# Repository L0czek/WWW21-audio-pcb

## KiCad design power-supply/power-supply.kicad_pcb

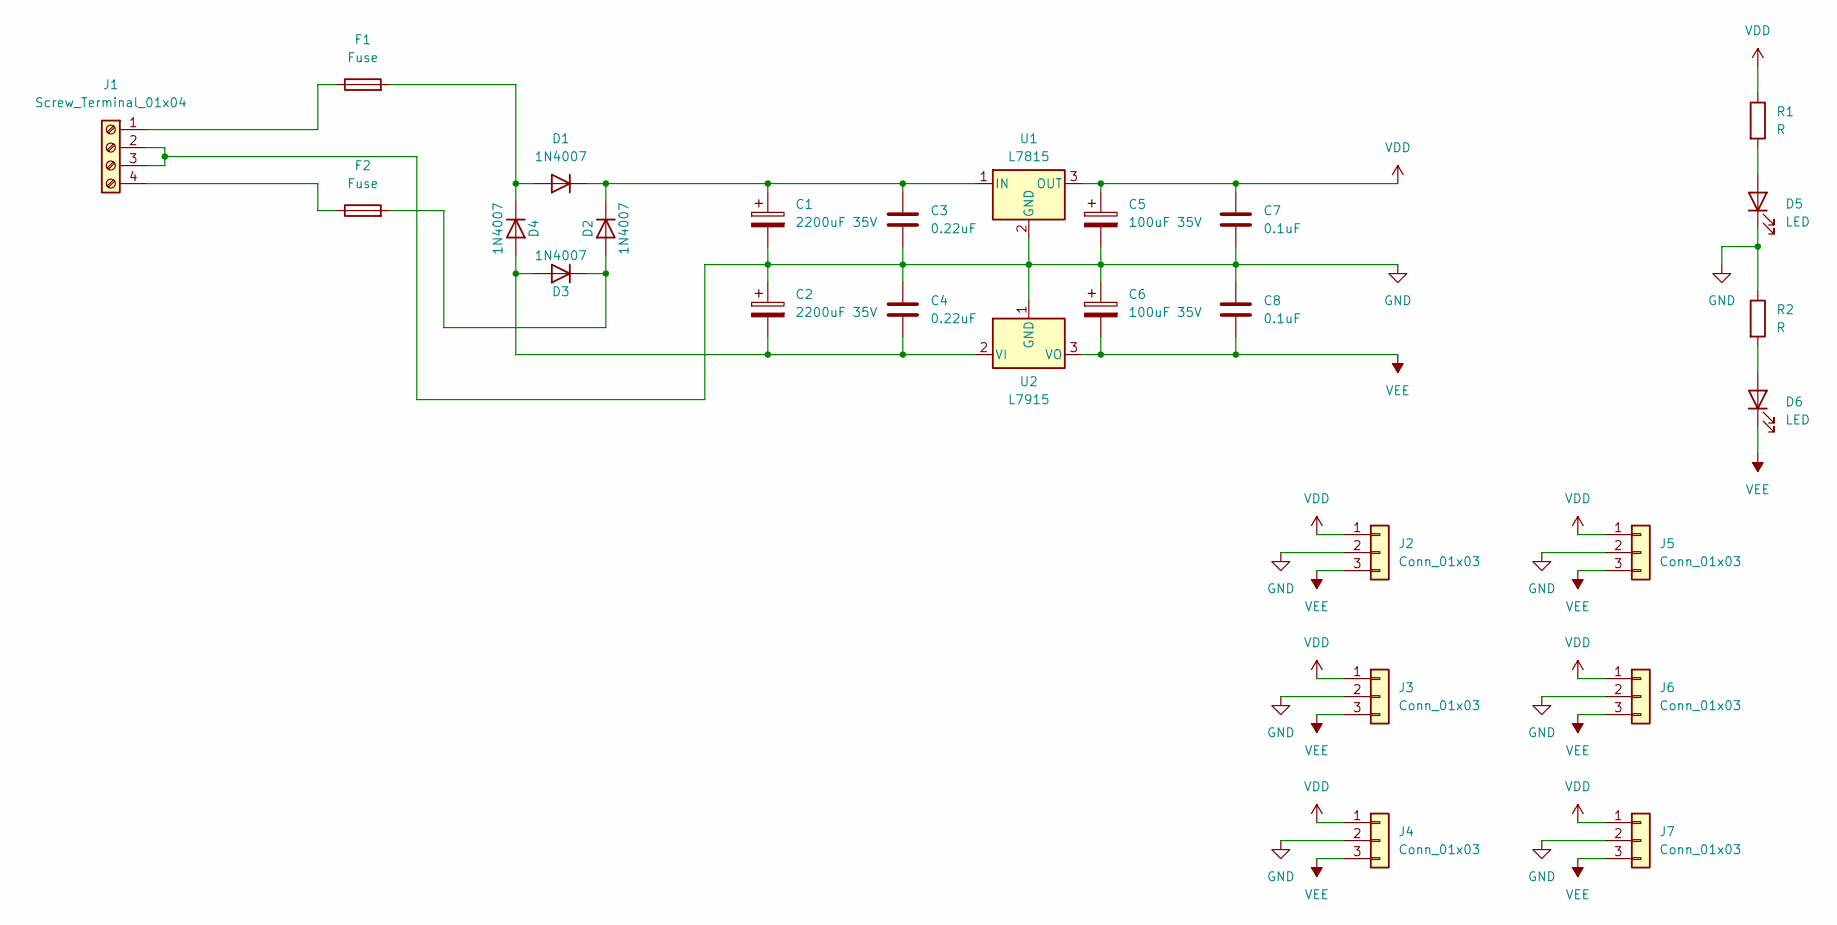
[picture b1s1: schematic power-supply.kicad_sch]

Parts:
C1, C2: 2200uF 35V; CP_Radial_D18.0mm_P7.50mm
C3, C4: 0.22uF; C_Disc_D5.0mm_W2.5mm_P5.00mm
C5, C6: 100uF 35V; CP_Radial_D10.0mm_P5.00mm
C7, C8: 0.1uF; C_Disc_D5.0mm_W2.5mm_P5.00mm
D1, D2, D3, D4: 1N4007; D_DO-41_SOD81_P10.16mm_Horizontal
D5, D6: LED; LED_D5.0mm
F1, F2: Fuse; R_Axial_DIN0207_L6.3mm_D2.5mm_P10.16mm_Horizontal
J1: Screw_Terminal_01x04; TerminalBlock_MaiXu_MX126-5.0-04P_1x04_P5.00mm
J2, J3, J4, J5, J6, J7: Conn_01x03; JST_PH_B3B-PH-K_1x03_P2.00mm_Vertical
R1, R2: R; R_Axial_DIN0207_L6.3mm_D2.5mm_P10.16mm_Horizontal
U1: L7815; TO-220-3_Vertical
U2: L7915; TO-220-3_Vertical

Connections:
GND: C1.2, C2.1, C3.2, C4.1, C5.2, C6.1, C7.2, C8.1, D5.1 (K), J1.2, J1.3, J2.2, J3.2, J4.2, J5.2, J6.2, J7.2, R2.1, U1.2 (GND), U2.1 (GND)
unnamed: D1.2 (A), D4.1 (K), F1.2
unnamed: C1.1, C3.1, D1.1 (K), D2.1 (K), U1.1 (IN)
unnamed: D2.2 (A), D3.1 (K), F2.2
unnamed: C2.2, C4.2, D3.2 (A), D4.2 (A), U2.2 (VI)
unnamed: D5.2 (A), R1.2
unnamed: D6.2 (A), R2.2
unnamed: F1.1, J1.1
unnamed: F2.1, J1.4
VDD: C5.1, C7.1, J2.1, J3.1, J4.1, J5.1, J6.1, J7.1, R1.1, U1.3 (OUT)
VEE: C6.2, C8.2, D6.1 (K), J2.3, J3.3, J4.3, J5.3, J6.3, J7.3, U2.3 (VO)

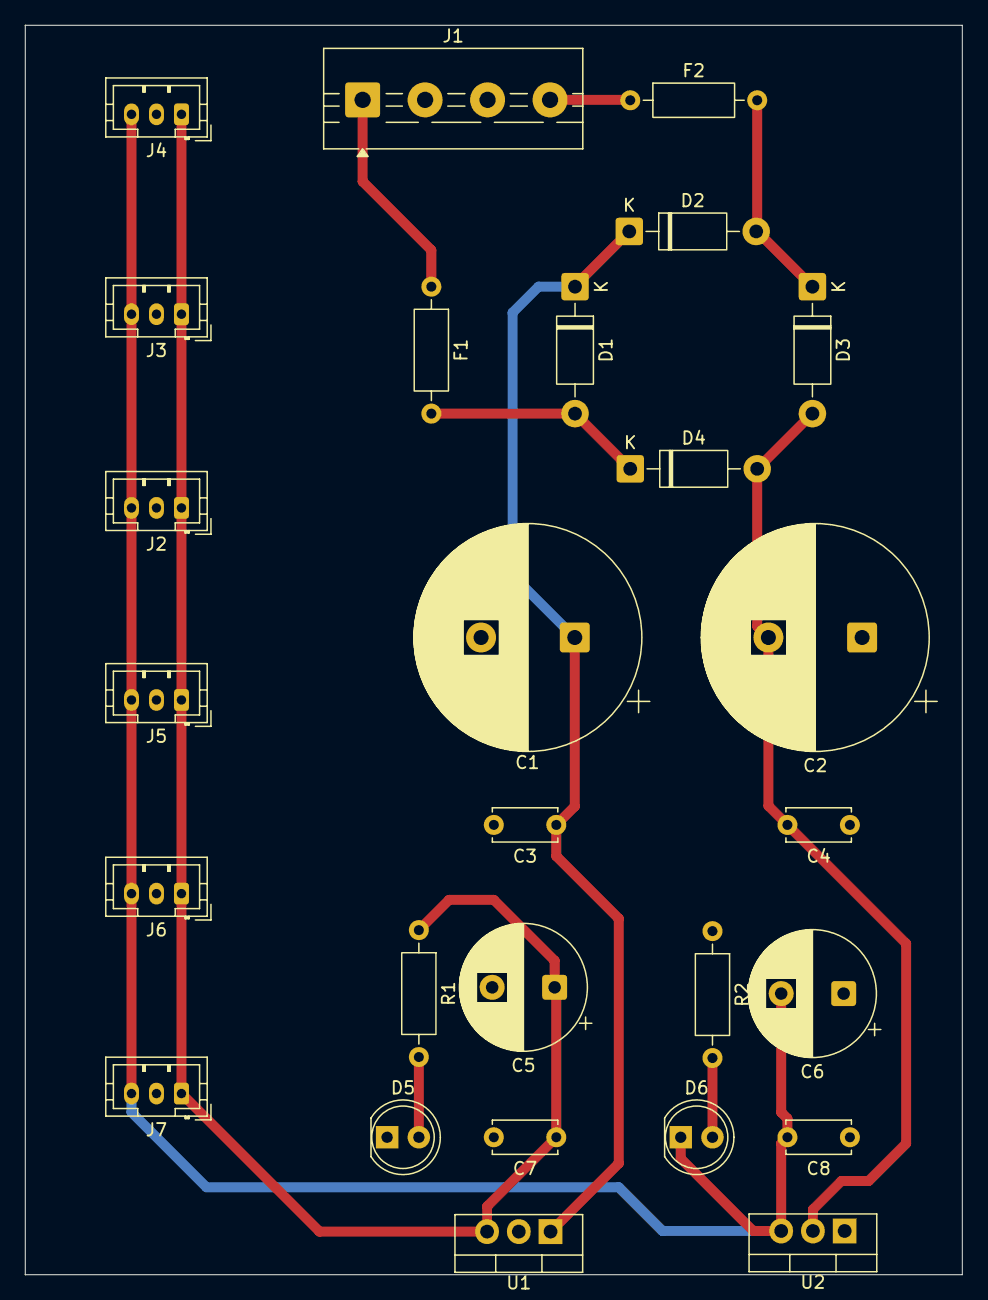
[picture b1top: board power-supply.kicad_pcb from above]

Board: 2 copper layers, 75.0 x 100.0 mm, 27 parts (0 on the bottom side), 11 nets.

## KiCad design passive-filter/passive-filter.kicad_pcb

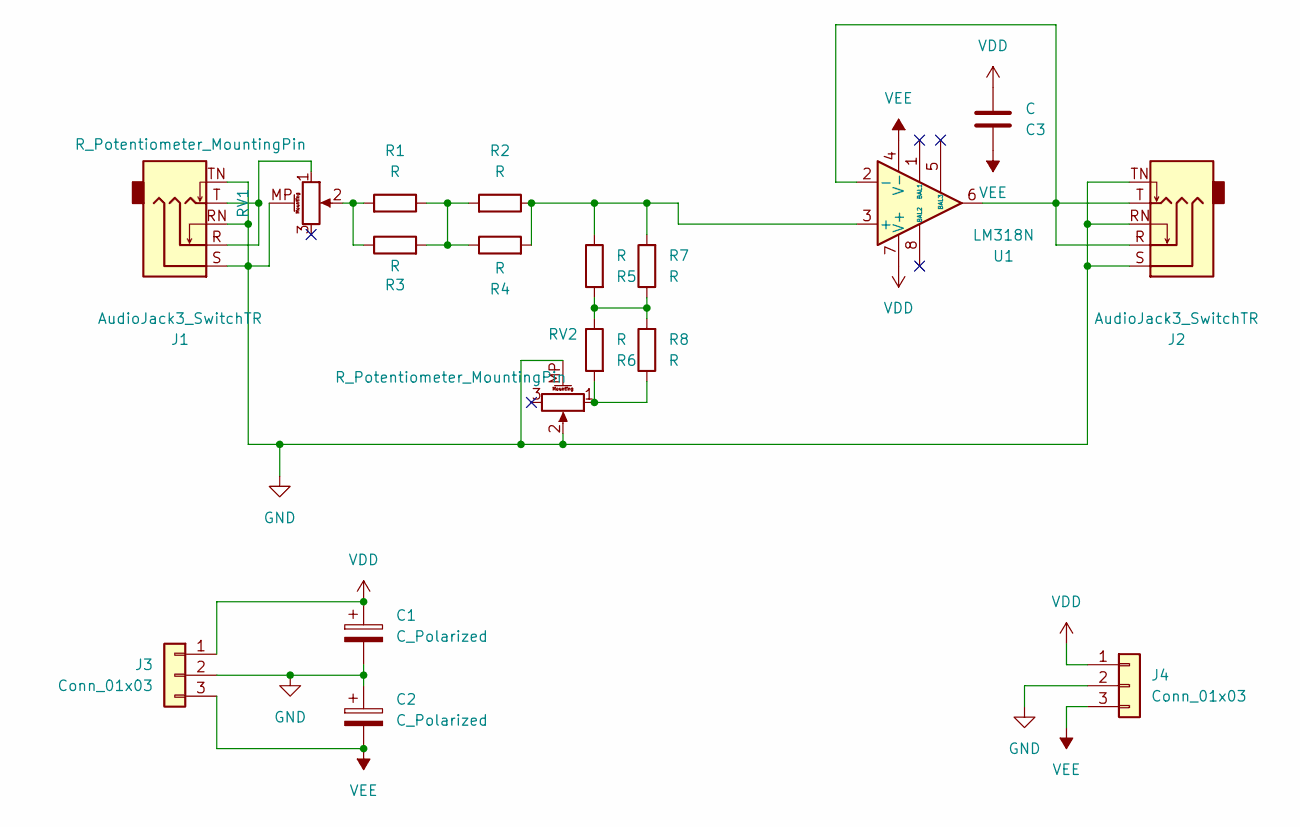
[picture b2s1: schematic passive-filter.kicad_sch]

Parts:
C1, C2: C_Polarized; CP_Radial_D10.0mm_P5.00mm
C3: C; C_Disc_D5.0mm_W2.5mm_P5.00mm
J1, J2: AudioJack3_SwitchTR; Jack_3.5mm_CUI_SJ1-3525N_Horizontal
J3, J4: Conn_01x03; JST_PH_B3B-PH-K_1x03_P2.00mm_Vertical
R1, R2, R3, R4, R5, R6, R7, R8: R; Universal-RLC
RV1, RV2: R_Potentiometer_MountingPin; Potentiometer_Bourns_PTV09A-1_Single_Vertical
U1: LM318N; DIP-8_W7.62mm_Socket_LongPads

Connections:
GND: C1.2, C2.1, J1.RN, J1.S, J1.TN, J2.RN, J2.S, J2.TN, J3.2, J4.2, RV1.MP (MountPin), RV2.2, RV2.MP (MountPin)
unnamed: J1.R, J1.T, RV1.1
unnamed: R1.1, R2.2, R3.2, R4.1
unnamed: R1.2, R3.1, RV1.2
unnamed: R5.2, R6.1, R7.1, R8.2
unnamed: R6.2, R8.1, RV2.1
unnamed: R2.1, R4.2, R5.1, R7.2, U1.3 (+)
unnamed: J2.R, J2.T, U1.2 (-), U1.6
VDD: C1.1, C3.2, J3.1, J4.1, U1.7 (V+)
VEE: C2.2, C3.1, J3.3, J4.3, U1.4 (V-)

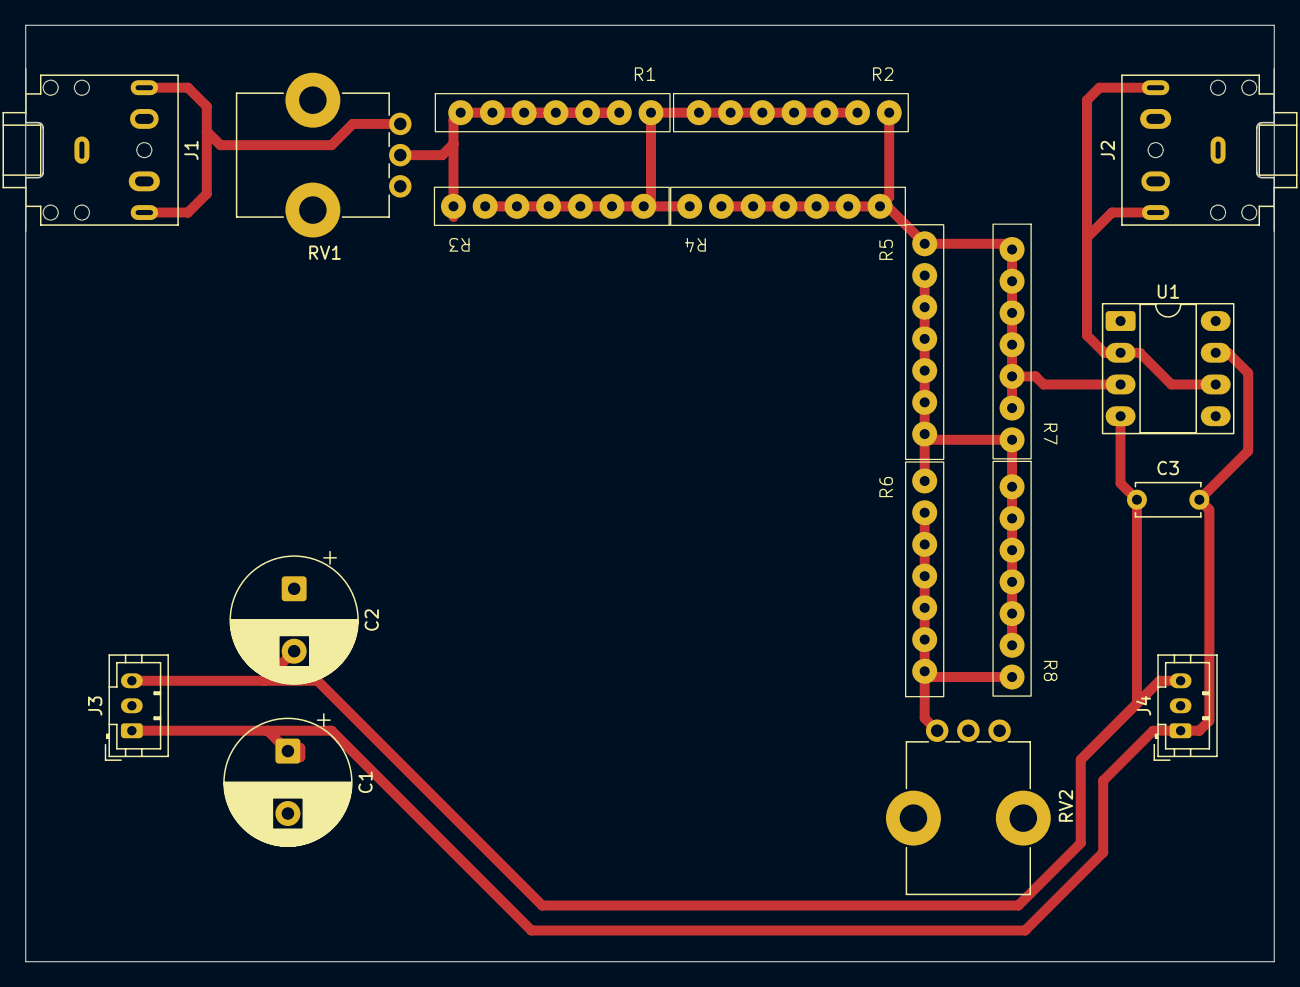
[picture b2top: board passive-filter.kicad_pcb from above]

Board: 2 copper layers, 100.0 x 74.9 mm, 18 parts (0 on the bottom side), 10 nets.

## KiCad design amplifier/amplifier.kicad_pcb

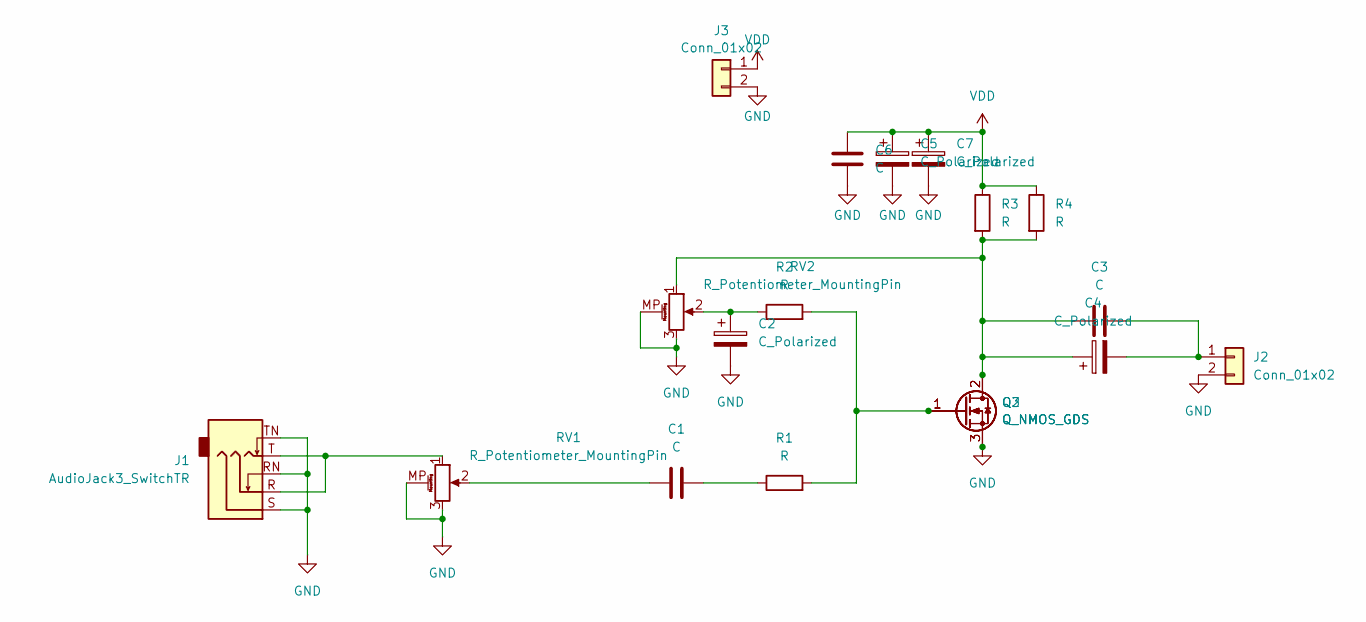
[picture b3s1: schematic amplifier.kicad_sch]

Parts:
C1, C6: C; C_Disc_D4.7mm_W2.5mm_P5.00mm
C2: C_Polarized; C_Radial_D10.0mm_H20.0mm_P5.00mm
C3: C; C_Rect_L33.0mm_W13.0mm_P27.50mm_MKS4
C4, C5, C7: C_Polarized; CP_Radial_D16.0mm_P7.50mm
J1: AudioJack3_SwitchTR; Jack_3.5mm_CUI_SJ1-3525N_Horizontal
J2: Conn_01x02; JST_NV_B02P-NV_1x02_P5.00mm_Vertical
J3: Conn_01x02; AMASS_XT30PW-M_1x02_P2.50mm_Horizontal
Q2: Q_NMOS_GDS; TO-247-3_Vertical
Q3: Q_NMOS_GDS; TO-220-3_Vertical
R1, R2: R; R_Axial_DIN0207_L6.3mm_D2.5mm_P15.24mm_Horizontal
R3, R4: R; R_Axial_Power_L75.0mm_W9.0mm_P86.36mm
RV1, RV2: R_Potentiometer_MountingPin; Potentiometer_Bourns_PTV09A-1_Single_Vertical

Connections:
GND: C2.2, C5.2, C6.2, C7.2, J1.RN, J1.S, J1.TN, J2.2, J3.2, Q2.3 (S), Q3.3 (S), RV1.3, RV1.MP (MountPin), RV2.3, RV2.MP (MountPin)
unnamed: C1.1, RV1.2
unnamed: C1.2, R1.1
unnamed: C2.1, R2.1, RV2.2
unnamed: J1.R, J1.T, RV1.1
unnamed: C3.2, C4.2, J2.1
unnamed: C3.1, C4.1, Q2.2 (D), Q3.2 (D), R3.2, R4.2, RV2.1
unnamed: Q2.1 (G), Q3.1 (G), R1.2, R2.2
VDD: C5.1, C6.1, C7.1, J3.1, R3.1, R4.1

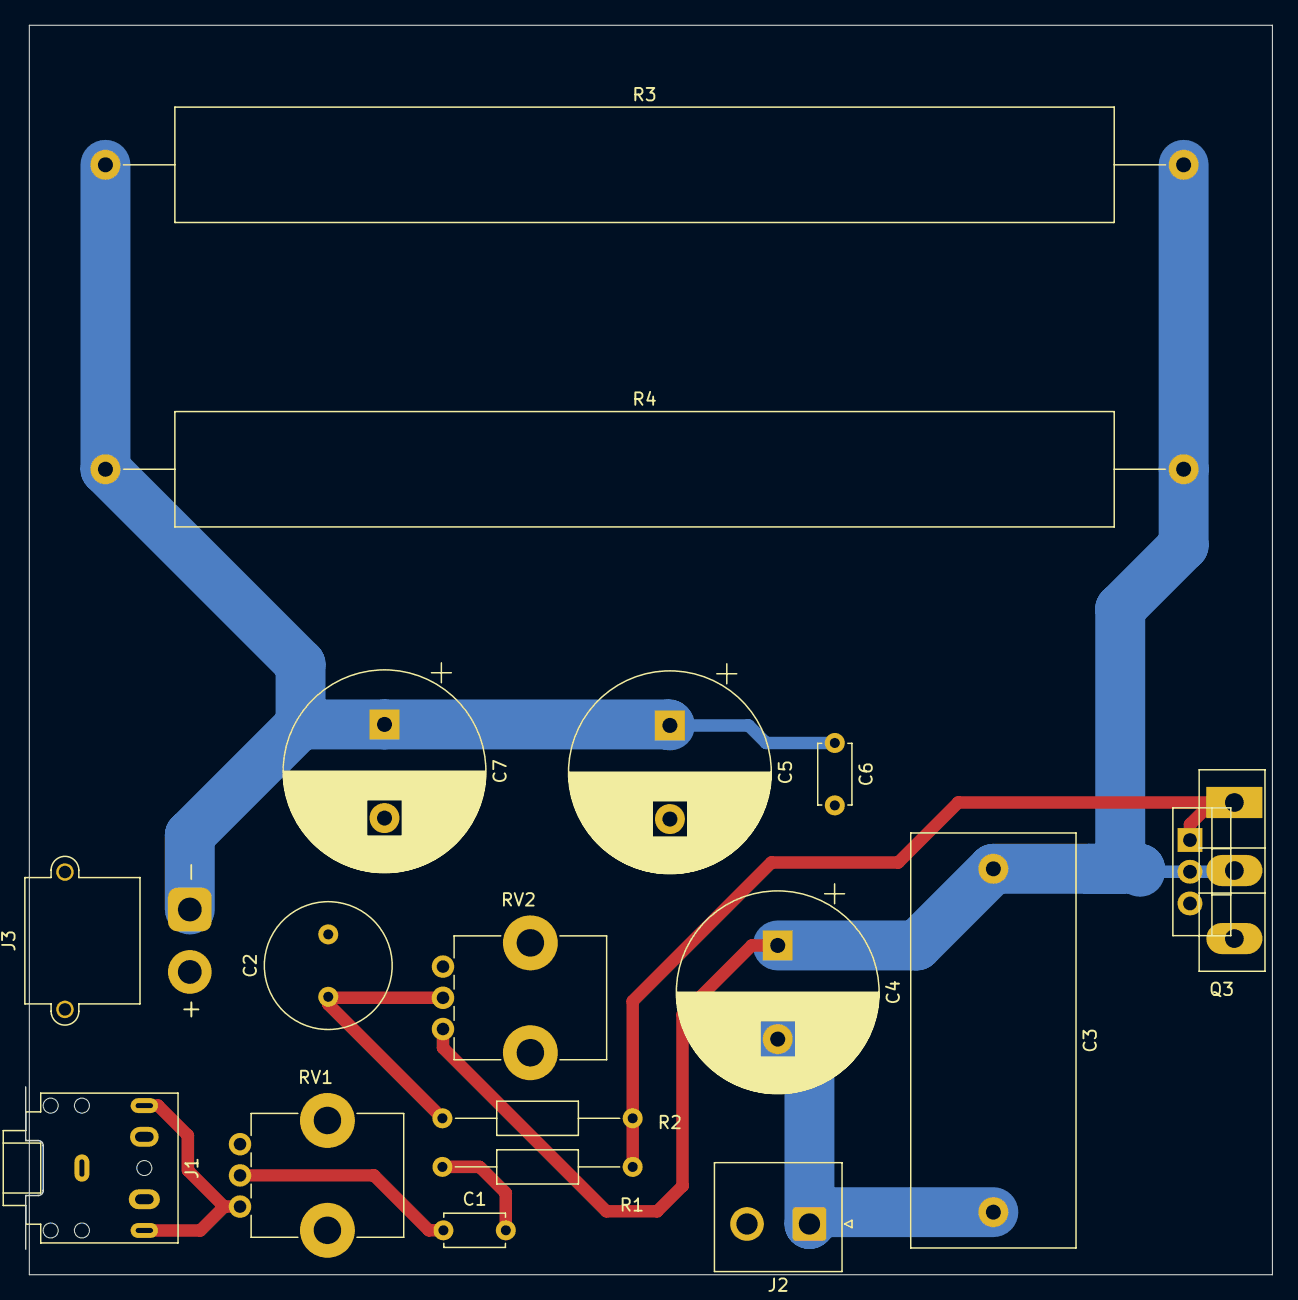
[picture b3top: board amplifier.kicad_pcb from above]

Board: 2 copper layers, 99.8 x 100.0 mm, 18 parts (0 on the bottom side), 9 nets.

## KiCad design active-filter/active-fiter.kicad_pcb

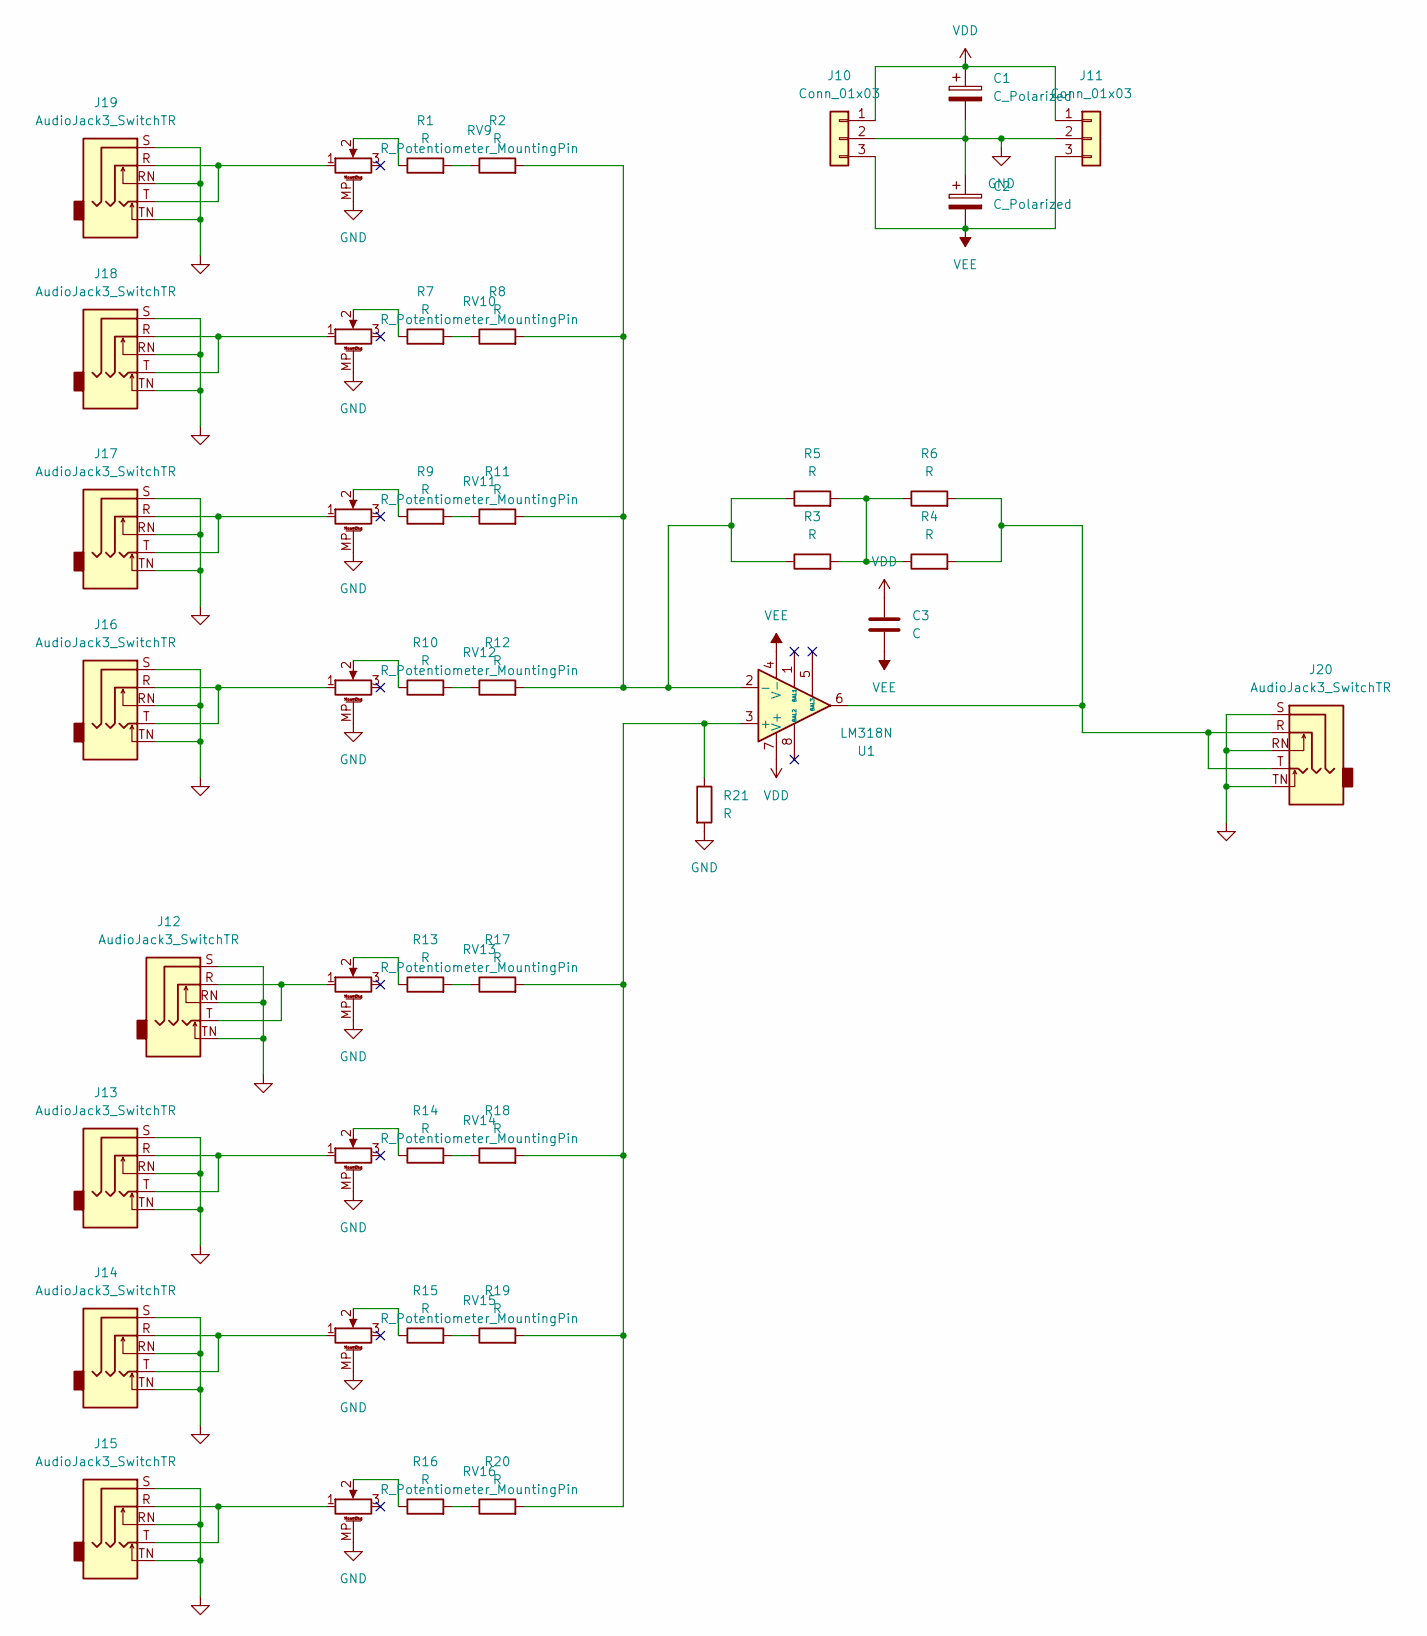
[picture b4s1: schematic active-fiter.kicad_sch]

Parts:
C1, C2: C_Polarized; CP_Radial_D10.0mm_P5.00mm
C3: C; C_Disc_D5.0mm_W2.5mm_P5.00mm
J10, J11: Conn_01x03; JST_PH_B3B-PH-K_1x03_P2.00mm_Vertical
J12, J13, J14, J15, J16, J17, J18, J19, J20: AudioJack3_SwitchTR; Jack_3.5mm_CUI_SJ1-3525N_Horizontal
R1, R2, R3, R4, R5, R6, R7, R8, R9, R10, R11, R12, R13, R14, R15, R16, R17, R18, R19, R20, R21: R; Universal-RLC
RV9, RV10, RV11, RV12, RV13, RV14, RV15, RV16: R_Potentiometer_MountingPin; Potentiometer_Bourns_PTV09A-1_Single_Vertical
U1: LM318N; DIP-8_W7.62mm_Socket_LongPads

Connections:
GND: C1.2, C2.1, J10.2, J11.2, J12.RN, J12.S, J12.TN, J13.RN, J13.S, J13.TN, J14.RN, J14.S, J14.TN, J15.RN, J15.S, J15.TN, J16.RN, J16.S, J16.TN, J17.RN, J17.S, J17.TN, J18.RN, J18.S, J18.TN, J19.RN, J19.S, J19.TN, J20.RN, J20.S, J20.TN, R21.2, RV9.MP (MountPin), RV10.MP (MountPin), RV11.MP (MountPin), RV12.MP (MountPin), RV13.MP (MountPin), RV14.MP (MountPin), RV15.MP (MountPin), RV16.MP (MountPin)
unnamed: J12.R, J12.T, RV13.1
unnamed: J13.R, J13.T, RV14.1
unnamed: J14.R, J14.T, RV15.1
unnamed: J15.R, J15.T, RV16.1
unnamed: J16.R, J16.T, RV12.1
unnamed: J17.R, J17.T, RV11.1
unnamed: J18.R, J18.T, RV10.1
unnamed: J19.R, J19.T, RV9.1
unnamed: J20.R, J20.T, R4.2, R6.2, U1.6
unnamed: R1.1, RV9.2
unnamed: R1.2, R2.1
unnamed: R3.2, R4.1, R5.2, R6.1
unnamed: R7.1, RV10.2
unnamed: R7.2, R8.1
unnamed: R9.1, RV11.2
unnamed: R10.1, RV12.2
unnamed: R10.2, R12.1
unnamed: R9.2, R11.1
unnamed: R13.1, RV13.2
unnamed: R13.2, R17.1
unnamed: R14.1, RV14.2
unnamed: R14.2, R18.1
unnamed: R15.1, RV15.2
unnamed: R15.2, R19.1
unnamed: R16.1, RV16.2
unnamed: R16.2, R20.1
unnamed: R17.2, R18.2, R19.2, R20.2, R21.1, U1.3 (+)
unnamed: R2.2, R3.1, R5.1, R8.2, R11.2, R12.2, U1.2 (-)
VDD: C1.1, C3.1, J10.1, J11.1, U1.7 (V+)
VEE: C2.2, C3.2, J10.3, J11.3, U1.4 (V-)

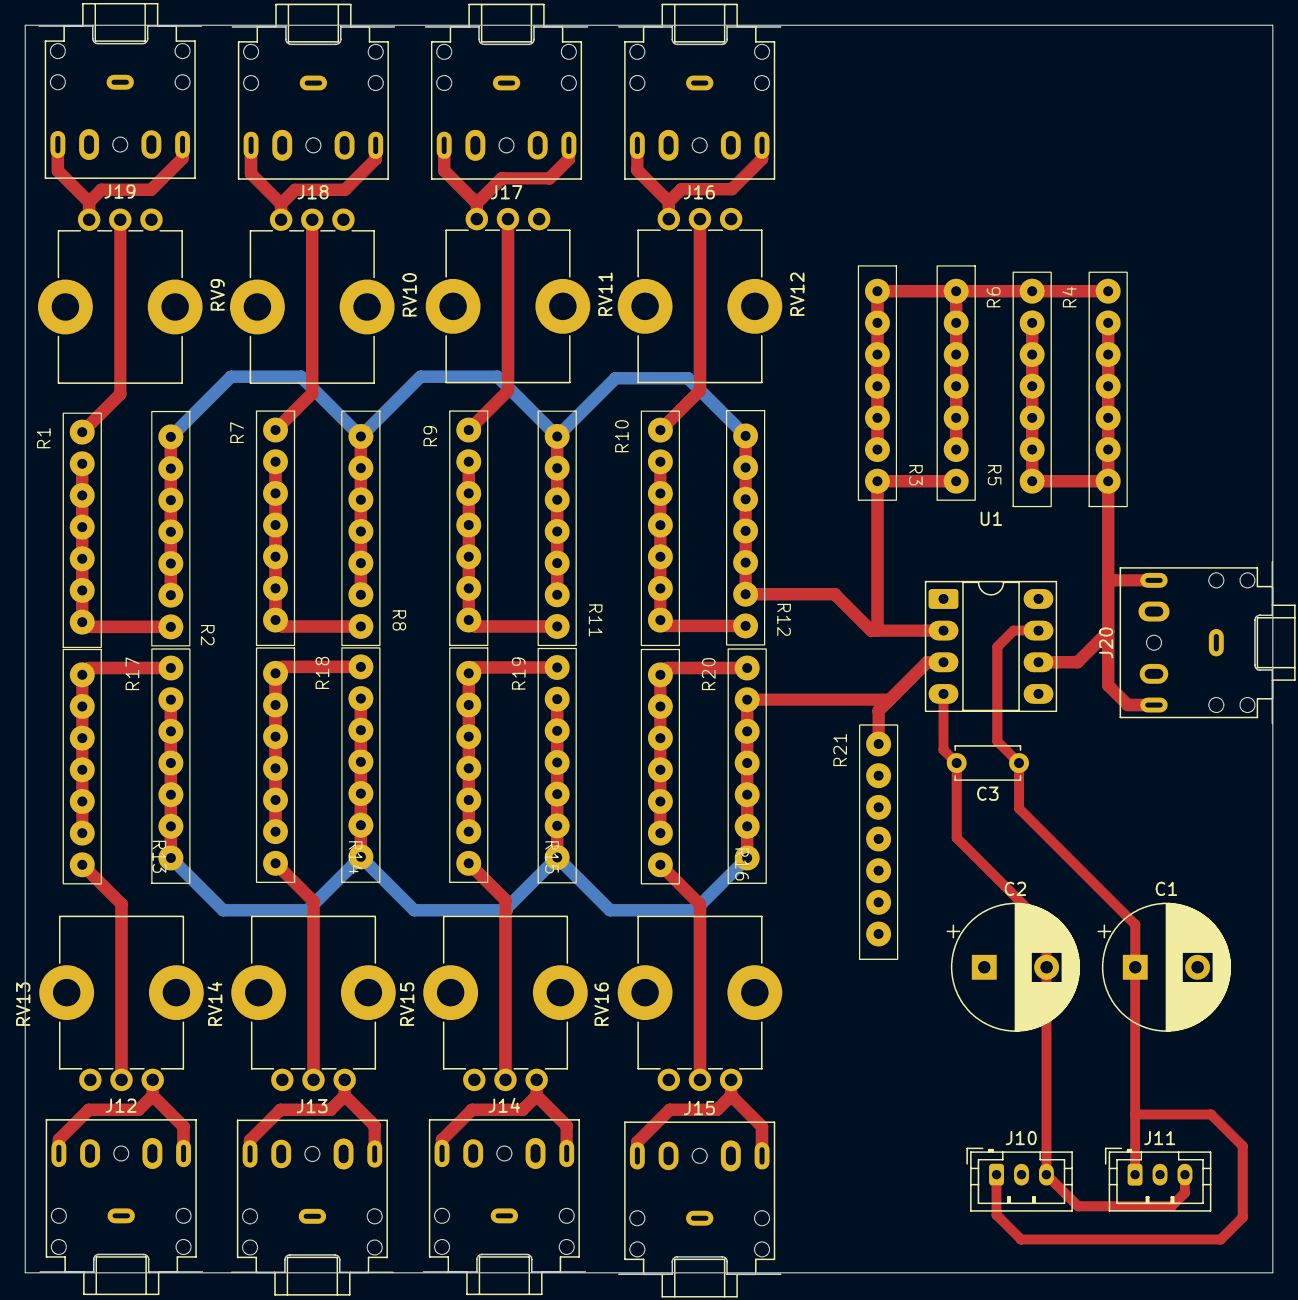
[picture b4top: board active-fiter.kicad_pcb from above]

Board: 2 copper layers, 100.0 x 100.2 mm, 44 parts (0 on the bottom side), 31 nets.

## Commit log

2025-06-22 Initial
2025-06-22 Add custom universal RLC component
2025-06-22 Add new custom pot lib
2025-06-22 Add passive filter schematic
2025-06-22 Start implementing active filter board
2025-06-22 passive-filter: Set footprints
2025-06-23 Add active filter pcb
2025-06-23 Add amplifier schematic
2025-06-23 Add amplifier pcb
2025-06-26 passive-filter: Add PCB
2025-06-26 passive-filter: Add PCB v2
2025-07-02 Add power-supply board
2025-07-02 power-supply: Improved version
2025-07-02 power-supply: Remove stupid leftover trace xd
